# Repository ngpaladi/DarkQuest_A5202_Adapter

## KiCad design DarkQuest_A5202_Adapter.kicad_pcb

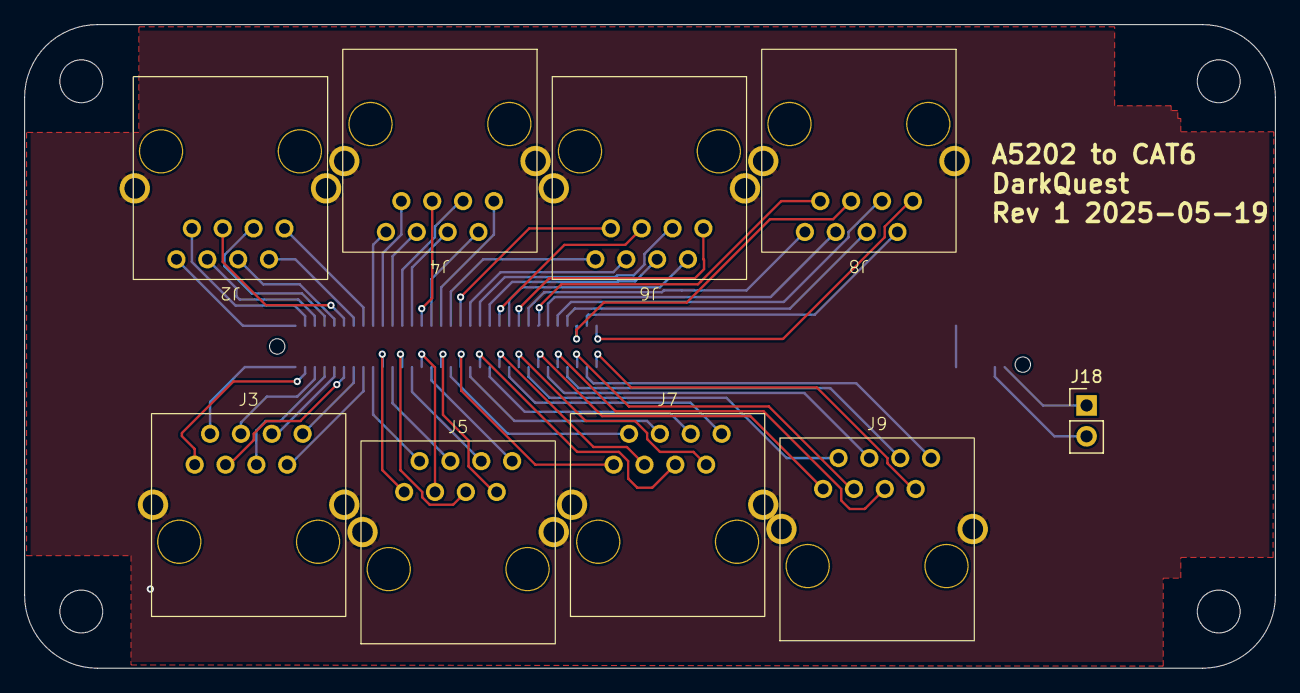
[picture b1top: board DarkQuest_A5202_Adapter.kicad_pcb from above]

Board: 2 copper layers, 103.0 x 53.0 mm, 10 parts (1 on the bottom side), 68 nets.

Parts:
J1: HSEC8-170-01-X-DV-A; SAMTEC_HSEC8-170-01-X-DV-A
J2, J3, J4, J5, J6, J7, J8, J9: RJ45_Shielded; RJJS-88-122-E7V-022
J18: Conn_01x02_Pin; PinHeader_1x02_P2.54mm_Vertical

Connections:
+3V3: J1.129, J1.130
/A0: J1.02, J2.8
/A1: J1.01, J3.2
/A2: J1.06, J2.6
/A3: J1.05, J3.4
/A4: J1.10, J2.4
/A5: J1.09, J3.6
/A6: J1.14, J2.2
/A7: J1.13, J3.8
/A8: J1.18, J4.8
/A9: J1.17, J5.2
/A10: J1.22, J4.6
/A11: J1.21, J5.4
/A12: J1.26, J4.4
/A13: J1.25, J5.6
/A14: J1.30, J4.2
/A15: J1.29, J5.8
/A16: J1.34, J6.8
/A17: J1.33, J7.2
/A18: J1.38, J6.6
/A19: J1.37, J7.4
/A20: J1.42, J6.4
/A21: J1.41, J7.6
/A22: J1.46, J6.2
/A23: J1.45, J7.8
/A24: J1.50, J8.8
/A25: J1.49, J9.2
/A26: J1.54, J8.6
/A27: J1.53, J9.4
/A28: J1.58, J8.4
/A29: J1.57, J9.6
/A30: J1.62, J8.2
/A31: J1.61, J9.8
/K0: J1.04, J2.7
/K1: J1.03, J3.1
/K2: J1.08, J2.3
/K3: J1.07, J3.5
/K4: J1.12, J2.5
/K5: J1.11, J3.3
/K6: J1.16, J2.1
/K7: J1.15, J3.7
/K8: J1.20, J4.7
/K9: J1.19, J5.1
/K10: J1.24, J4.3
/K11: J1.23, J5.5
/K12: J1.28, J4.5
/K13: J1.27, J5.3
/K14: J1.32, J4.1
/K15: J1.31, J5.7
/K16: J1.36, J6.7
/K17: J1.35, J7.1
/K18: J1.40, J6.3
/K19: J1.39, J7.5
/K20: J1.44, J6.5
/K21: J1.43, J7.3
/K22: J1.48, J6.1
/K23: J1.47, J7.7
/K24: J1.52, J8.7
/K25: J1.51, J9.1
/K26: J1.56, J8.3
/K27: J1.55, J9.5
/K28: J1.60, J8.5
/K29: J1.59, J9.3
/K30: J1.64, J8.1
/K31: J1.63, J9.7
/Therm_Avail: J1.137, J18.2
/Therm_Sig: J1.139, J18.1
GND: J1.131, J1.132, J1.134, J1.136, J1.138, J1.140, J2.SH, J3.SH, J4.SH, J5.SH, J6.SH, J7.SH, J8.SH, J9.SH

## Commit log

2025-05-21 RJ45v1
2025-06-11 Added stencil
